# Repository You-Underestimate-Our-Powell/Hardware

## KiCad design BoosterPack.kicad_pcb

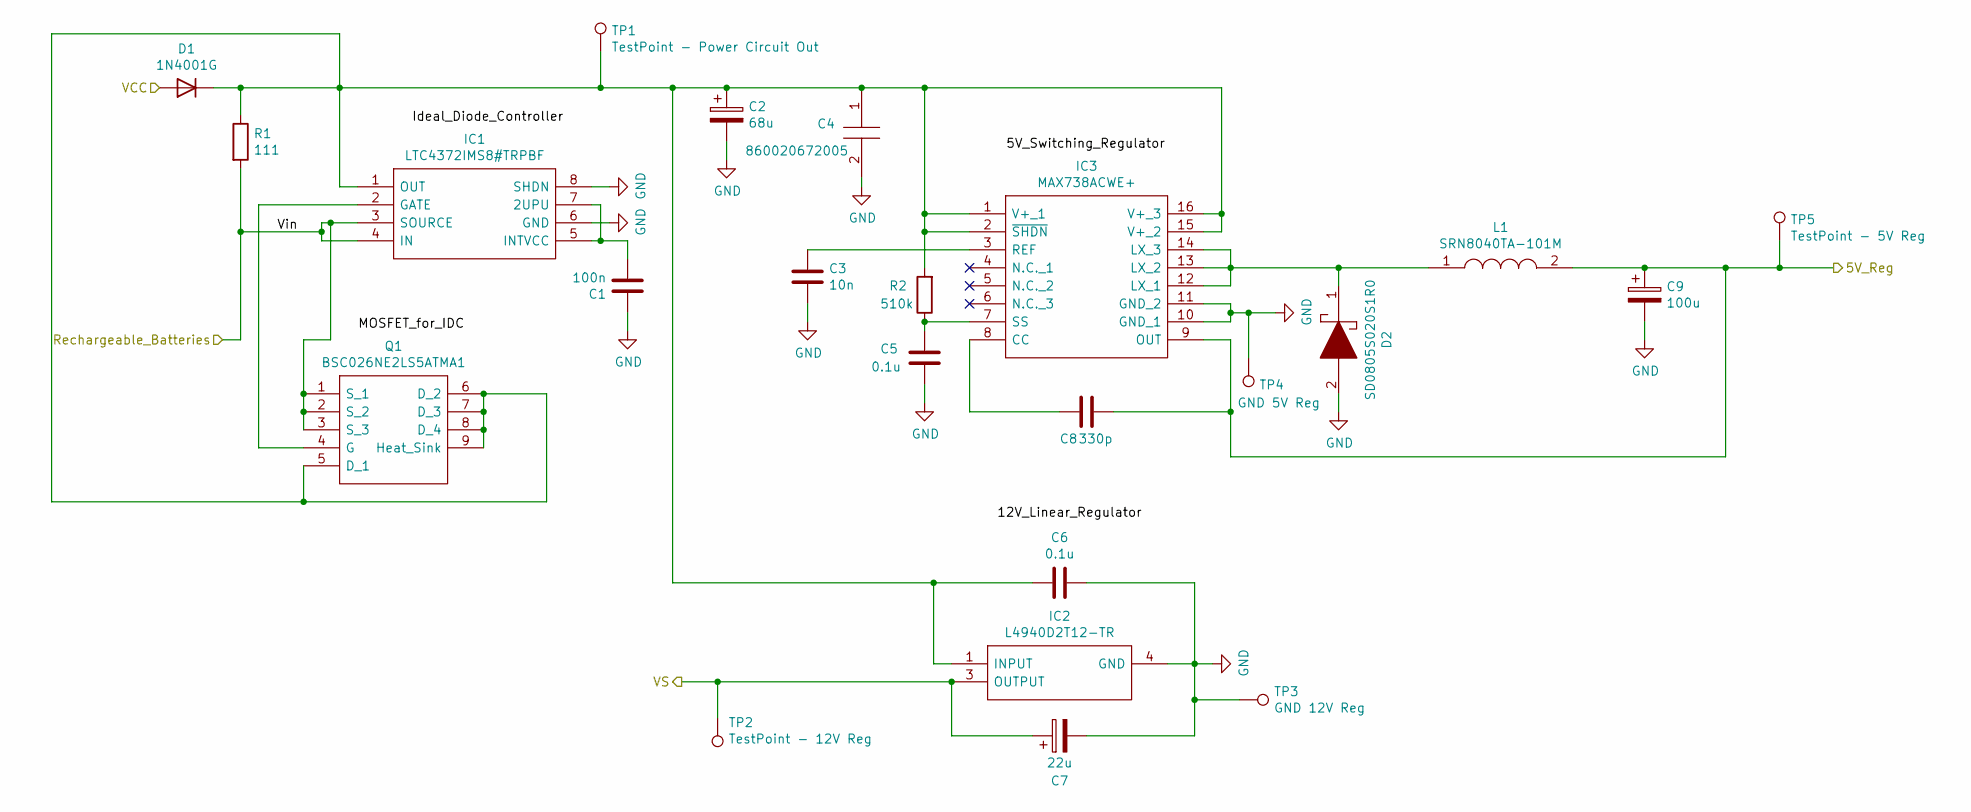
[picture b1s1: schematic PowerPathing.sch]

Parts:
C1: 100n; C_Rect_L7.0mm_W2.5mm_P5.00mm
C2: 68u; CAPPRD200W52D500H1250
C3: 10n; C_Rect_L7.0mm_W2.5mm_P5.00mm
C4: 860020672005; CAPPRD200W52D500H1250; Manufacturer_Part_Number 860020672005; Mouser Part Number 710-860020672005
C5, C6: 0.1u; C_Rect_L7.0mm_W2.5mm_P5.00mm
C7: 22u; CAPPRD200W52D500H1250
C8: 330p; C_Rect_L7.0mm_W2.5mm_P5.00mm
C9: 100u; CAPPRD200W52D500H1250
D1: 1N4001G; D_0805_2012Metric_Pad1.15x1.40mm_HandSolder
D2: SD0805S020S1R0; DIOM1613X100N; Manufacturer_Part_Number SD0805S020S1R0; Mouser Part Number 581-SD0805S020S1R0
IC1: LTC4372IMS8#TRPBF; SOP65P490X110-8N; Manufacturer_Part_Number LTC4372IMS8#TRPBF; Mouser Part Number 584-LTC4372IMS8TRPBF
IC2: L4940D2T12-TR; TO254P1542X460-3N; Manufacturer_Part_Number L4940D2T12-TR; Mouser Part Number 511-L4940D2T12-TR
IC3: MAX738ACWE+; SOIC127P1032X265-16N; Manufacturer_Part_Number MAX738ACWE+; Mouser Part Number 700-MAX738ACWE
L1: SRN8040TA-101M; INDPM8080X450N; Manufacturer_Part_Number SRN8040TA-101M; Mouser Part Number 652-SRN8040TA-101M
Q1: BSC026NE2LS5ATMA1; Manufacturer_Part_Number BSC026NE2LS5ATMA1; Mouser Part Number 726-BSC026NE2LS5ATMA
R1: 111; RESAD1650W60L650D250
R2: 510k; RESAD1650W60L650D250
TP1: TestPoint - Power Circuit Out; TestPoint_Loop_D2.60mm_Drill1.6mm_Beaded
TP2: TestPoint - 12V Reg; TestPoint_Loop_D2.60mm_Drill1.6mm_Beaded
TP3: GND 12V Reg; TestPoint_Loop_D2.60mm_Drill1.6mm_Beaded
TP4: GND 5V Reg; TestPoint_Loop_D2.60mm_Drill1.6mm_Beaded
TP5: TestPoint - 5V Reg; TestPoint_Loop_D2.60mm_Drill1.6mm_Beaded

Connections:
/Connectors/5V_Reg: C8.1, C9.1, IC3.9 (OUT), L1.2, TP5.1; also elsewhere on the board
/Connectors/Rechargeable_Batteries: IC1.3 (SOURCE), IC1.4 (IN), Q1.1 (S_1), Q1.2 (S_2), Q1.3 (S_3), R1.2; also elsewhere on the board
/Connectors/VCC: D1.2 (A); also elsewhere on the board
/Connectors/VS: C7.1, IC2.3 (OUTPUT), TP2.1; also elsewhere on the board
GND: C1.1, C2.2, C3.2, C4.2, C5.2, C6.1, C7.2, C9.2, D2.2, IC1.6 (GND), IC1.8 (SHDN), IC2.4 (GND), IC3.10 (GND_1), IC3.11 (GND_2), TP3.1, TP4.1; also elsewhere on the board
unnamed: C1.2, IC1.5 (INTVCC), IC1.7 (2UPU)
unnamed: C2.1, C4.1, C6.2, D1.1 (K), IC1.1 (OUT), IC2.1 (INPUT), IC3.1 (V+_1), IC3.2 (~SHDN), IC3.15 (V+_2), IC3.16 (V+_3), Q1.5 (D_1), Q1.6 (D_2), Q1.7 (D_3), Q1.8 (D_4), Q1.9 (Heat_Sink), R1.1, R2.2, TP1.1
unnamed: C3.1, IC3.3 (REF)
unnamed: C5.1, IC3.7 (SS), R2.1
unnamed: C8.2, IC3.8 (CC)
unnamed: D2.1, IC3.12 (LX_1), IC3.13 (LX_2), IC3.14 (LX_3), L1.1
unnamed: IC1.2 (GATE), Q1.4 (G)

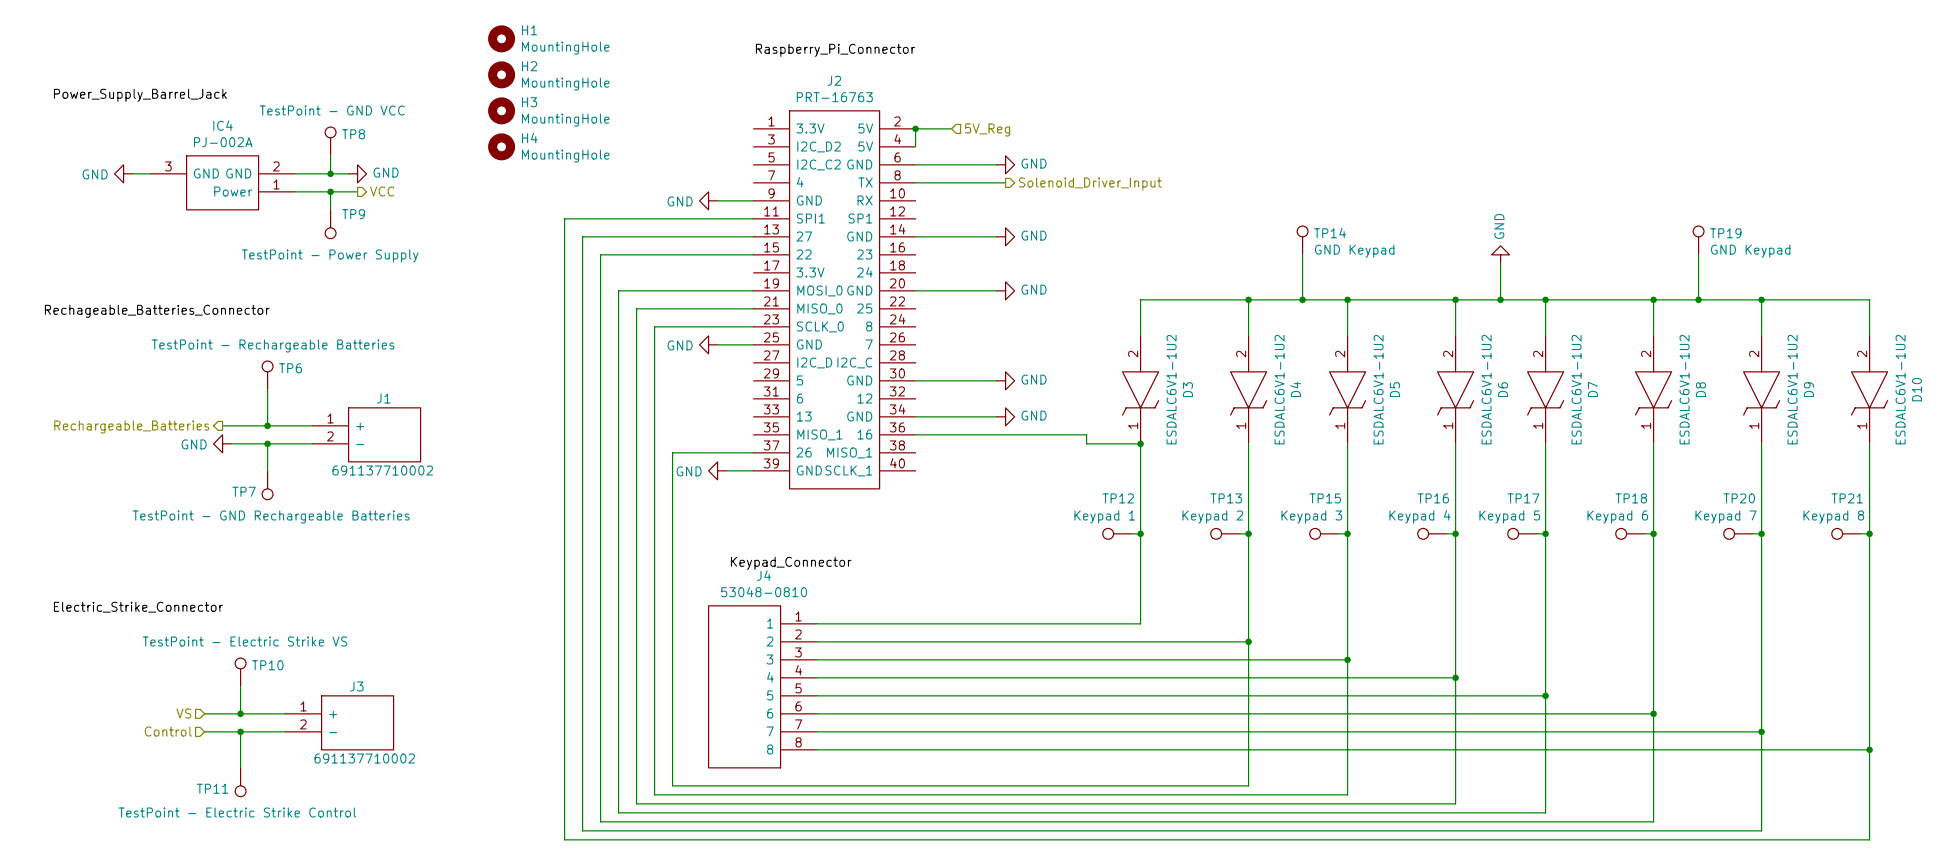
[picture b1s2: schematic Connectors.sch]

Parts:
D3, D4, D5, D6, D7, D8, D9, D10: ESDALC6V1-1U2; ESDALC6V11U2; Manufacturer_Part_Number ESDALC6V1-1U2; Mouser Part Number 511-ESDALC6V1-1U2
H1, H2, H3, H4: MountingHole; MountingHole_2.7mm_M2.5_Pad
IC4: PJ-002A; PJ002A; Manufacturer_Part_Number PJ-002A; Mouser Part Number 490-PJ-002A
J1, J3: 691137710002; SHDR2W70P0X500_1X2_1000X750X1160P; Manufacturer_Part_Number 691137710002; Mouser Part Number 710-691137710002
J2: PRT-16763; RHDR40W64P254_2X20_5130X500X1625P; Manufacturer_Part_Number PRT-16763; Mouser Part Number 474-PRT-16763
J4: 53048-0810; 530480810; Manufacturer_Part_Number 53048-0810
TP6: TestPoint - Rechargeable Batteries; TestPoint_Loop_D2.60mm_Drill1.6mm_Beaded
TP7: TestPoint - GND Rechargeable Batteries; TestPoint_Loop_D2.60mm_Drill1.6mm_Beaded
TP8: TestPoint - GND VCC; TestPoint_Loop_D2.60mm_Drill1.6mm_Beaded
TP9: TestPoint - Power Supply; TestPoint_Loop_D2.60mm_Drill1.6mm_Beaded
TP10: TestPoint - Electric Strike VS; TestPoint_Loop_D2.60mm_Drill1.6mm_Beaded
TP11: TestPoint - Electric Strike Control; TestPoint_Loop_D2.60mm_Drill1.6mm_Beaded
TP12: Keypad 1; TestPoint_Loop_D2.60mm_Drill1.6mm_Beaded
TP13: Keypad 2; TestPoint_Loop_D2.60mm_Drill1.6mm_Beaded
TP14, TP19: GND Keypad; TestPoint_Loop_D2.60mm_Drill1.6mm_Beaded
TP15: Keypad 3; TestPoint_Loop_D2.60mm_Drill1.6mm_Beaded
TP16: Keypad 4; TestPoint_Loop_D2.60mm_Drill1.6mm_Beaded
TP17: Keypad 5; TestPoint_Loop_D2.60mm_Drill1.6mm_Beaded
TP18: Keypad 6; TestPoint_Loop_D2.60mm_Drill1.6mm_Beaded
TP20: Keypad 7; TestPoint_Loop_D2.60mm_Drill1.6mm_Beaded
TP21: Keypad 8; TestPoint_Loop_D2.60mm_Drill1.6mm_Beaded

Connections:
/Connectors/5V_Reg: J2.2 (5V), J2.4 (5V); also elsewhere on the board
/Connectors/Control: J3.2 (-), TP11.1; also elsewhere on the board
/Connectors/Rechargeable_Batteries: J1.1 (+), TP6.1; also elsewhere on the board
/Connectors/Solenoid_Driver_Input: J2.8 (TX); also elsewhere on the board
/Connectors/VCC: IC4.1 (Power), TP9.1; also elsewhere on the board
/Connectors/VS: J3.1 (+), TP10.1; also elsewhere on the board
GND: D3.2, D4.2, D5.2, D6.2, D7.2, D8.2, D9.2, D10.2, IC4.2 (GND), IC4.3 (GND), J1.2 (-), J2.6 (GND), J2.9 (GND), J2.14 (GND), J2.20 (GND), J2.25 (GND), J2.30 (GND), J2.34 (GND), J2.39 (GND), TP7.1, TP8.1, TP14.1, TP19.1; also elsewhere on the board
unnamed: D3.1, J2.36 (16), J4.1, TP12.1
unnamed: D4.1, J2.37 (26), J4.2, TP13.1
unnamed: D5.1, J2.23 (SCLK_0), J4.3, TP15.1
unnamed: D6.1, J2.21 (MISO_0), J4.4, TP16.1
unnamed: D7.1, J2.19 (MOSI_0), J4.5, TP17.1
unnamed: D8.1, J2.15 (22), J4.6, TP18.1
unnamed: D9.1, J2.13 (27), J4.7, TP20.1
unnamed: D10.1, J2.11 (SPI1), J4.8, TP21.1

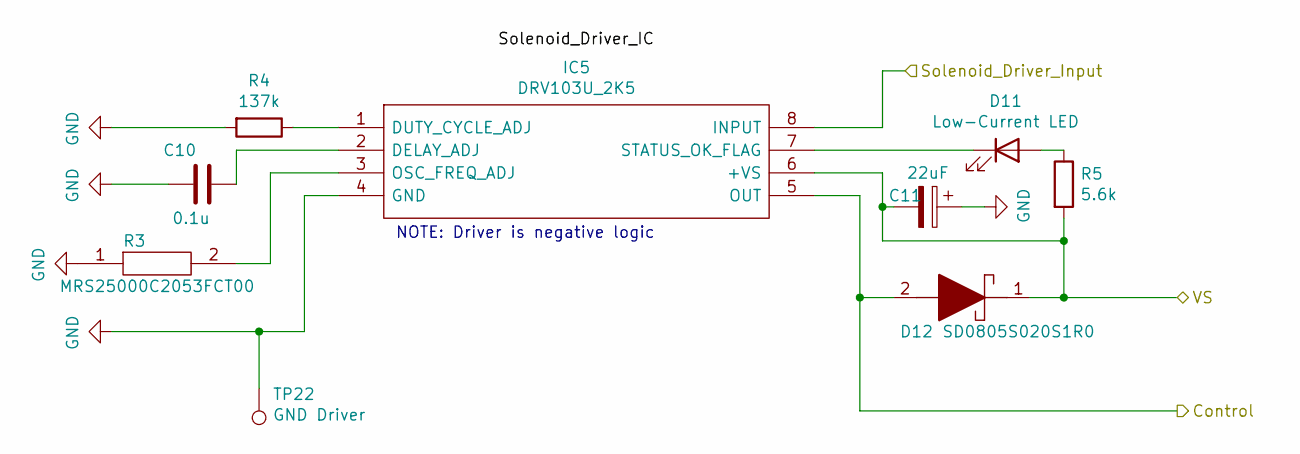
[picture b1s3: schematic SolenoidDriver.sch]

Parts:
C10: 0.1u; C_Rect_L7.0mm_W2.5mm_P5.00mm
C11: 22uF; CAPPRD200W52D500H1250
D11: Low-Current LED; D_0805_2012Metric_Pad1.15x1.40mm_HandSolder
D12: SD0805S020S1R0; DIOM1613X100N; Manufacturer_Part_Number SD0805S020S1R0; Mouser Part Number 581-SD0805S020S1R0
IC5: DRV103U_2K5; SOIC127P600X175-8N; Manufacturer_Part_Number DRV103U/2K5; Mouser Part Number 595-DRV103U/2K5
R3: MRS25000C2053FCT00; RESAD1650W60L650D250; Manufacturer_Part_Number MRS25000C2053FCT00
R4: 137k; RESAD1650W60L650D250
R5: 5.6k; RESAD1650W60L650D250
TP22: GND Driver; TestPoint_Loop_D2.60mm_Drill1.6mm_Beaded

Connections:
/Connectors/Control: D12.2, IC5.5 (OUT); also elsewhere on the board
/Connectors/Solenoid_Driver_Input: IC5.8 (INPUT); also elsewhere on the board
/Connectors/VS: C11.2, D12.1, IC5.6 (+VS), R5.2; also elsewhere on the board
GND: C10.2, C11.1, IC5.4 (GND), R3.1, R4.2, TP22.1; also elsewhere on the board
unnamed: C10.1, IC5.2 (DELAY_ADJ)
unnamed: D11.1 (K), IC5.7 (STATUS_OK_FLAG)
unnamed: D11.2 (A), R5.1
unnamed: IC5.1 (DUTY_CYCLE_ADJ), R4.1
unnamed: IC5.3 (OSC_FREQ_ADJ), R3.2

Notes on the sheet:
NOTE: Driver is negative logic

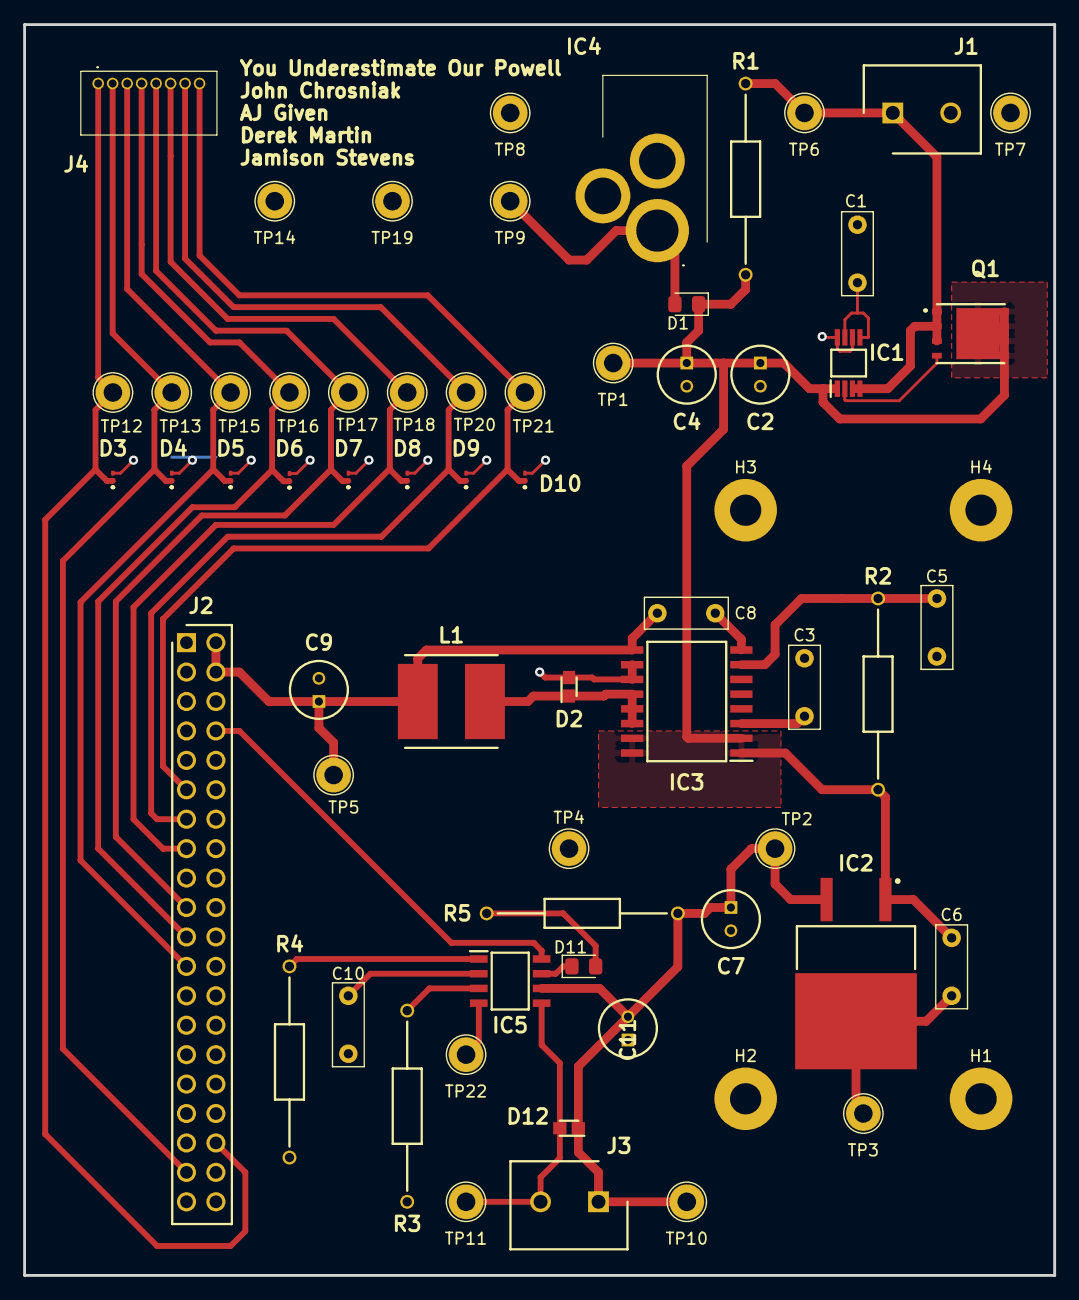
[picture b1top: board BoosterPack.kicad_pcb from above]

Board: 2 copper layers, 88.9 x 107.9 mm, 65 parts (0 on the bottom side), 27 nets.

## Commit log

2021-09-24 initial commit; added part for solenoid driver
2021-09-28 Added parts to library
2021-09-28 finished solenoid driver schematic, started power pathing and connectors
2021-09-30 Added components to library
2021-10-05 Schematic Updates
2021-10-05 Schematic Updates, still need component values for driver circuit and keypad connector EDA
2021-10-05 Schematic Updates, still need keypad connector EDA
2021-10-06 Added zener diode to library
2021-10-06 Add files via upload
    Bill of Materials, don't know how to open it :/
2021-10-06 added bill of materials
2021-10-06 Added Generic Keypad Connector, don't know if we can use it or not
2021-10-06 Added labels for ease of reading and reorganized a sheet, still have a Generic Keypad Connector, don't know if we can use it or not
2021-10-06 added connector to schematic
2021-10-07 Started schematic development
2021-10-13 initial commit for layout
2021-10-13 changed inductor used in power circuitry
2021-10-18 work on layout
2021-10-19 Preliminary Board Layout, no ground plane or traces yet
2021-10-19 Added all traces except 1 trace that needs a via and all connections to ground
2021-10-19 Finished first attempt at routing
2021-10-19 Fixed unconnected parts
2021-10-20 Board Layout Revisions: moved left two mounting holes a couple mm to right, moved trace connected to Pin 36 of Pi a little bit
2021-10-21 final edits for rev 1
2021-10-21 Updated silkscreen
2021-10-21 Moved Silkscreen Component Labels off of traces
2021-11-02 which parts we have
